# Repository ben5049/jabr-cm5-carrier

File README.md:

# Compute Module 5 Carrier Board (WIP)

Compact CM5 carrier board with an M.2 E-key connector and a 1000BASE-T1 ethernet PHY, as well as other optional IO.

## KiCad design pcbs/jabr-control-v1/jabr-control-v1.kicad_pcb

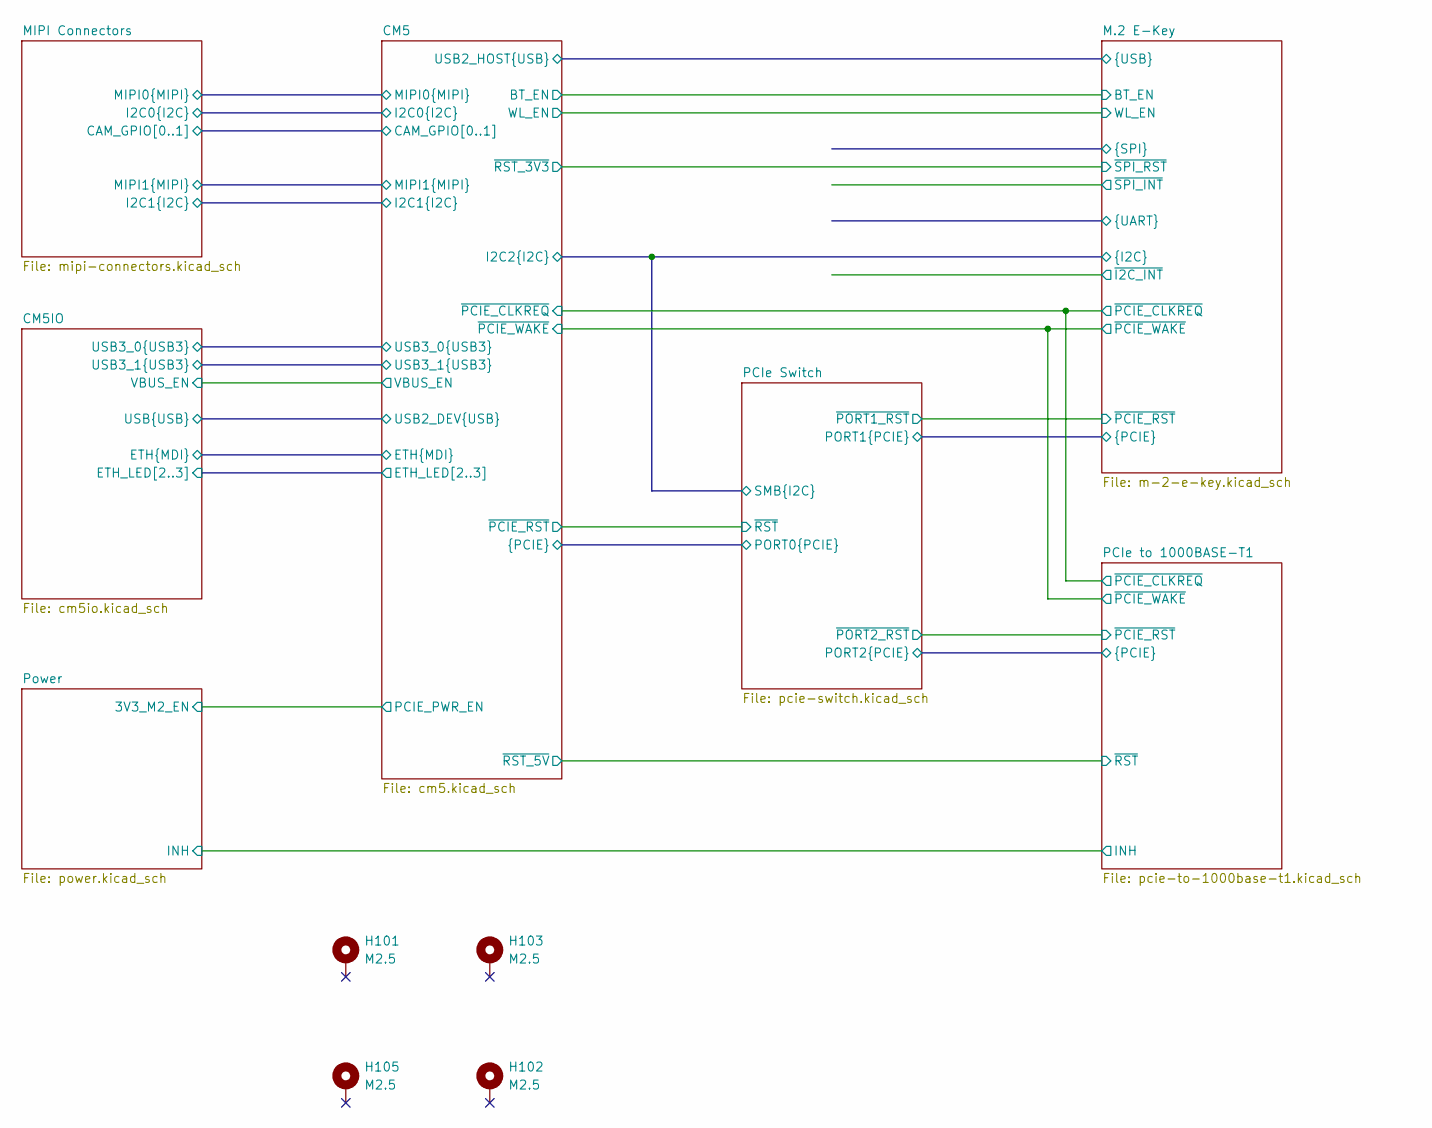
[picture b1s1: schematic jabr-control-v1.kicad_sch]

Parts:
H101, H102, H103, H105: M2.5; MountingHole_2.7mm_M2.5_Pad

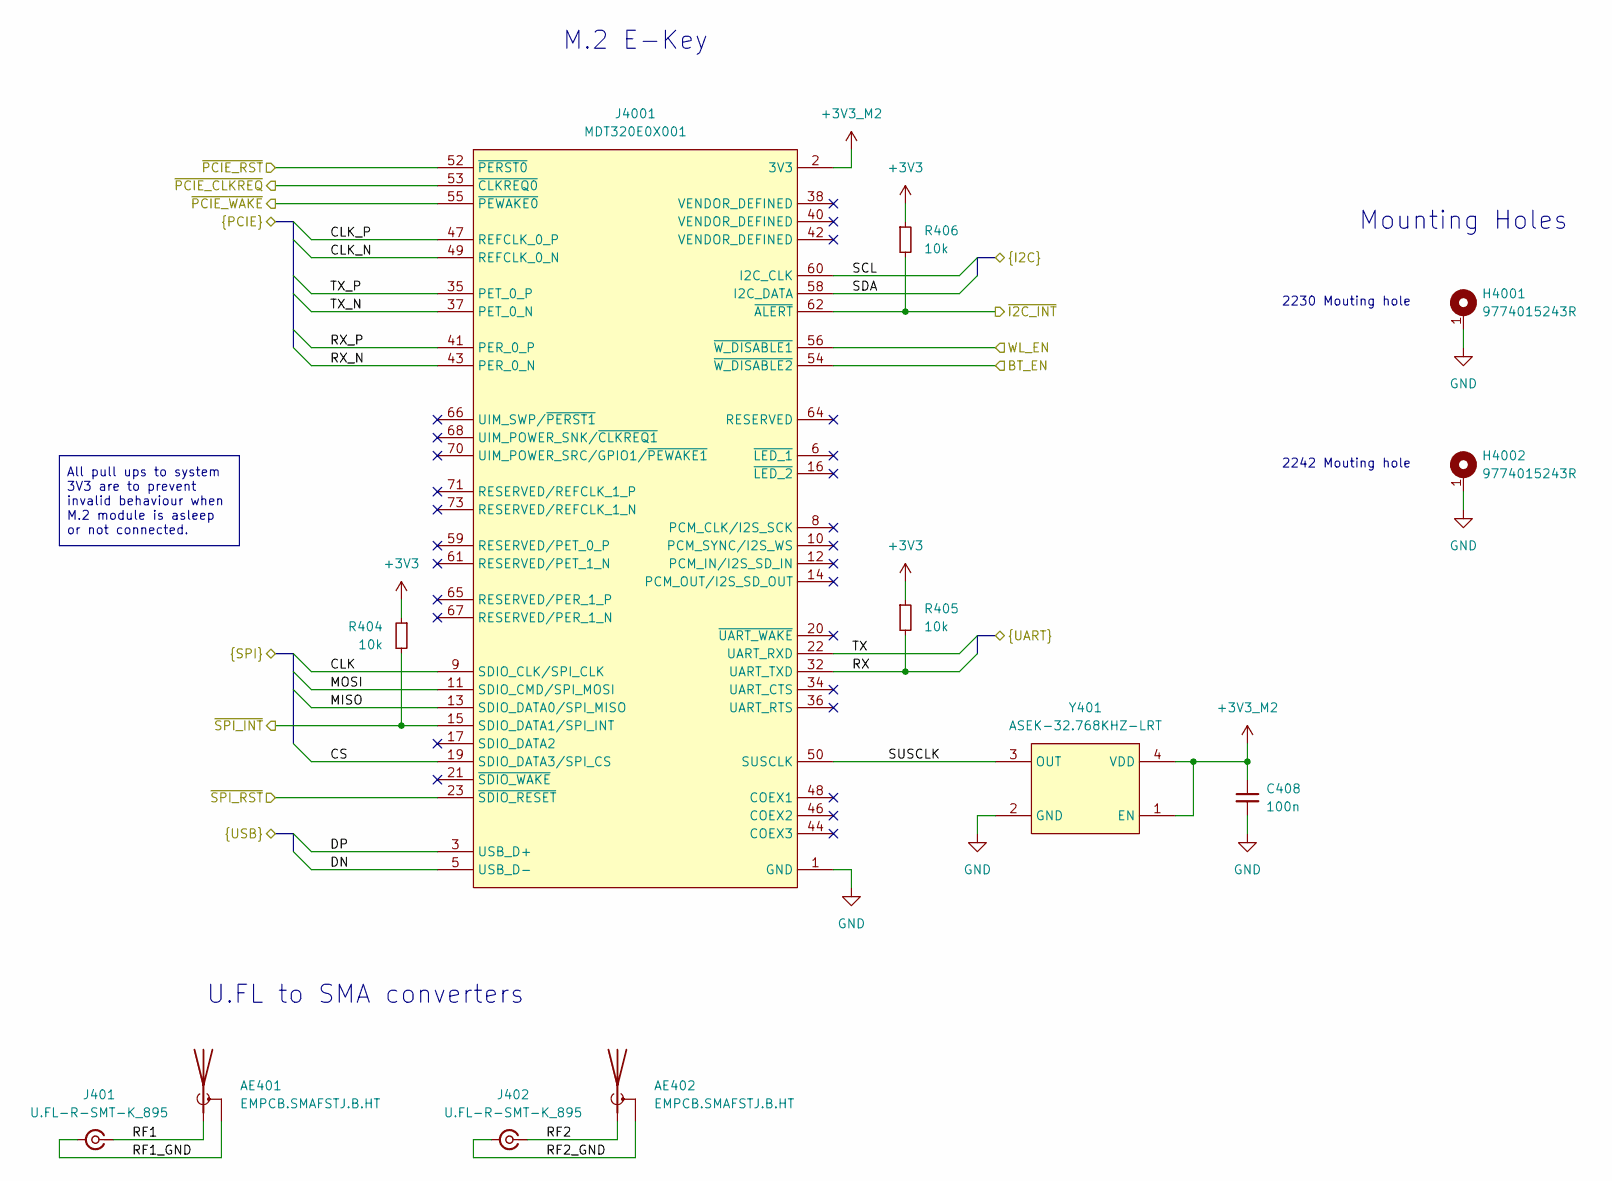
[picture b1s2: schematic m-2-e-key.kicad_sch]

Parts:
AE401, AE402: EMPCB.SMAFSTJ.B.HT; sma_edge_mount
C408: 100n
H4001, H4002: 9774015243R; 9774025243R
J401, J402: U.FL-R-SMT-K_895; UFLRSMTK895
J4001: MDT320E0X001; MDT420E0X001
R404, R405, R406: 10k; R_0402
Y401: ASEK-32.768KHZ-LRT; Crystal_SMD_3225-4Pin_3.2x2.5mm

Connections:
+3V3: R404.1, R405.1, R406.1; also elsewhere on the board
+3V3_M2: C408.1, J4001.2 (3V3), J4001.4 (3V3), J4001.72 (3V3), J4001.74 (3V3), Y401.1 (EN), Y401.4 (VDD); also elsewhere on the board
/CM5/BT_EN: J4001.54 (~W_DISABLE2); also elsewhere on the board
/CM5/I2C2.SCL: J4001.60 (I2C_CLK); also elsewhere on the board
/CM5/I2C2.SDA: J4001.58 (I2C_DATA); also elsewhere on the board
/CM5/USB2_HOST.DN: J4001.5 (USB_D-); also elsewhere on the board
/CM5/USB2_HOST.DP: J4001.3 (USB_D+); also elsewhere on the board
/CM5/WL_EN: J4001.56 (~W_DISABLE1); also elsewhere on the board
/CM5/~PCIE_CLKREQ: J4001.53 (~CLKREQ0); also elsewhere on the board
/CM5/~PCIE_WAKE: J4001.55 (~PEWAKE0); also elsewhere on the board
/CM5/~RST_3V3: J4001.23 (~SDIO_RESET); also elsewhere on the board
/M.2 E-Key/CLK: J4001.9 (SDIO_CLK/SPI_CLK)
/M.2 E-Key/CLK_N: J4001.49 (REFCLK_0_N); also elsewhere on the board
/M.2 E-Key/CLK_P: J4001.47 (REFCLK_0_P); also elsewhere on the board
/M.2 E-Key/CS: J4001.19 (SDIO_DATA3/SPI_CS)
/M.2 E-Key/MISO: J4001.13 (SDIO_DATA0/SPI_MISO)
/M.2 E-Key/MOSI: J4001.11 (SDIO_CMD/SPI_MOSI)
/M.2 E-Key/RF1: AE401.1 (A), J401.1 (In)
/M.2 E-Key/RF1_GND: AE401.2 (Shield), J401.2 (Ext)
/M.2 E-Key/RF2: AE402.1 (A), J402.1 (In)
/M.2 E-Key/RF2_GND: AE402.2 (Shield), J402.2 (Ext)
/M.2 E-Key/RX: J4001.32 (UART_TXD), R405.2
/M.2 E-Key/RX_N: J4001.43 (PER_0_N); also elsewhere on the board
/M.2 E-Key/RX_P: J4001.41 (PER_0_P); also elsewhere on the board
/M.2 E-Key/SUSCLK: J4001.50 (SUSCLK), Y401.3 (OUT)
/M.2 E-Key/TX: J4001.22 (UART_RXD)
/M.2 E-Key/TX_N: J4001.37 (PET_0_N); also elsewhere on the board
/M.2 E-Key/TX_P: J4001.35 (PET_0_P); also elsewhere on the board
/M.2 E-Key/~I2C_INT: J4001.62 (~ALERT), R406.2
/M.2 E-Key/~PCIE_RST: J4001.52 (~PERST0); also elsewhere on the board
/M.2 E-Key/~SPI_INT: J4001.15 (SDIO_DATA1/SPI_INT), R404.2
GND: C408.2, H4001.1, H4002.1, J4001.1 (GND), J4001.7 (GND), J4001.18 (GND), J4001.33 (GND), J4001.39 (GND), J4001.45 (GND), J4001.51 (GND), J4001.57 (GND), J4001.63 (GND), J4001.69 (GND), J4001.75 (GND), Y401.2 (GND); also elsewhere on the board

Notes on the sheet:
M.2 E-Key
2242 Mouting hole
U.FL to SMA converters
Mounting Holes
2230 Mouting hole
All pull ups to system 3V3 are to prevent invalid behaviour when M.2 module is asleep or not connected.

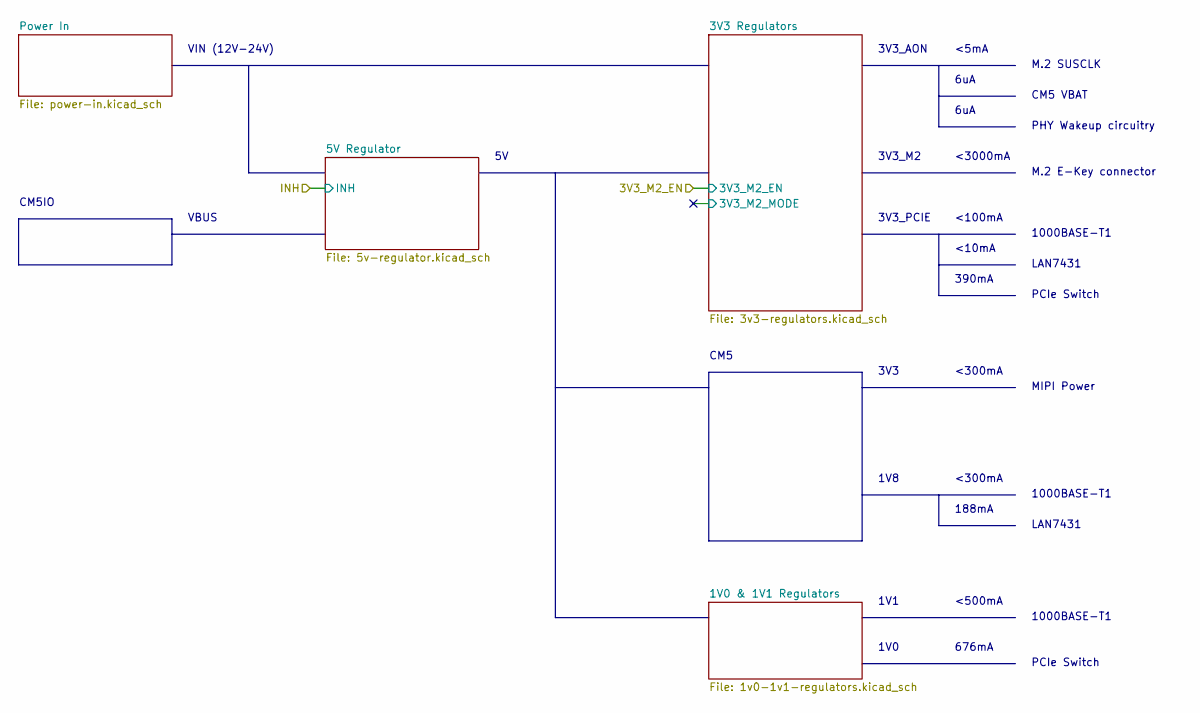
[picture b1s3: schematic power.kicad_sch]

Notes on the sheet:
PHY Wakeup circuitry
PCIe Switch
676mA
VBUS
<100mA
3V3
<300mA
6uA
3V3_M2
LAN7431
1V1
CM5IO
<5mA
1000BASE-T1
188mA
M.2 E-Key connector
3V3_PCIE
M.2 SUSCLK
<10mA
VIN (12V-24V)
<500mA
1V8
<3000mA
CM5 VBAT
3V3_AON
1V0
390mA
CM5
MIPI Power

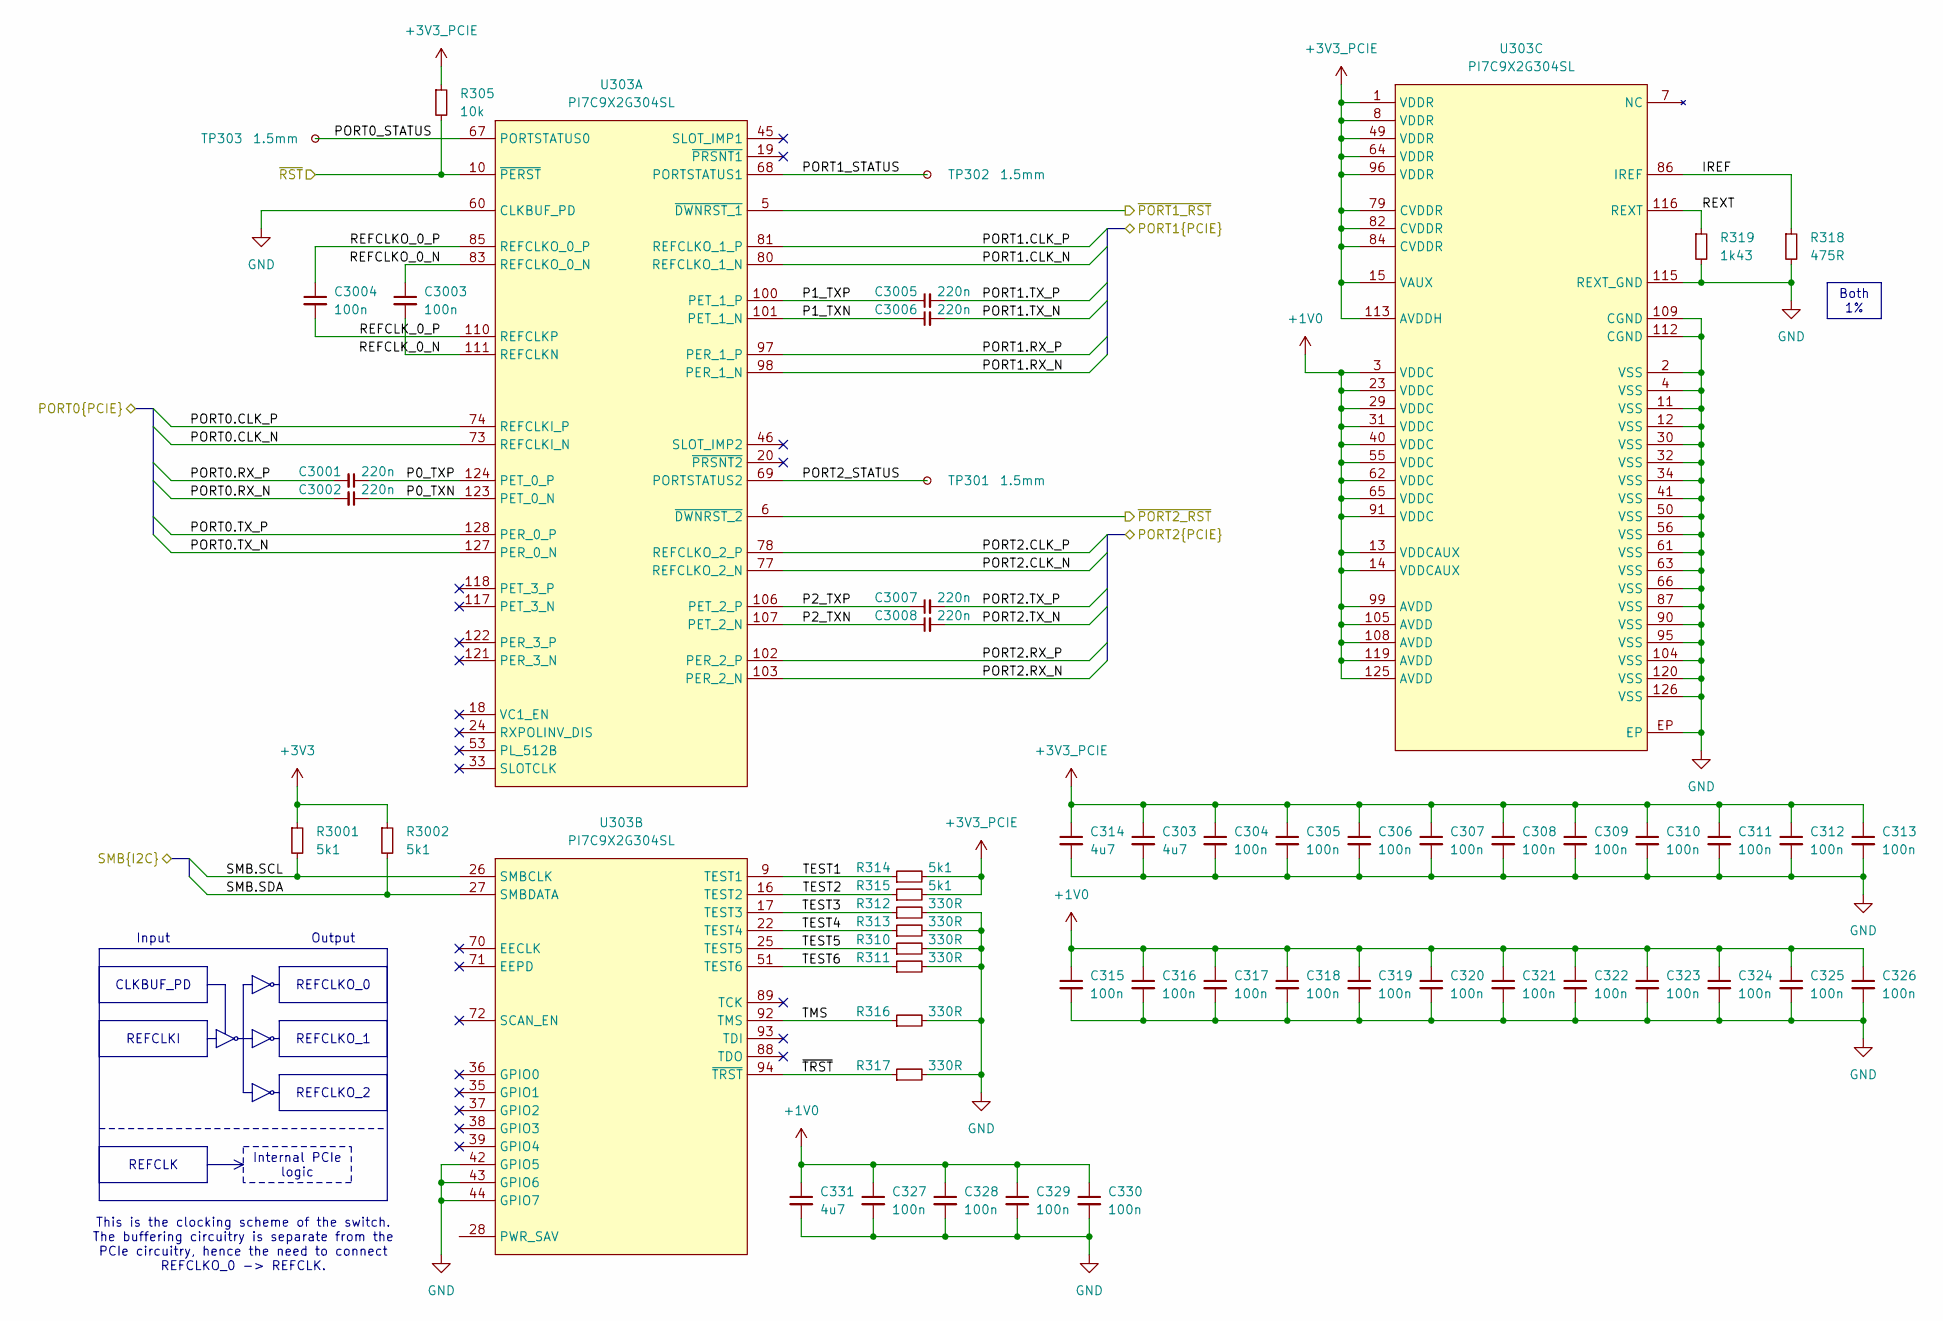
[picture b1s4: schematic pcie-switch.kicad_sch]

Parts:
C303, C314, C331: 4u7; C_0402
C304, C305, C306, C307, C308, C309, C310, C311, C312, C313, C315, C316, C317, C318, C319, C320, C321, C322, C323, C324, C325, C326, C327, C328, C329, C330, C3003, C3004: 100n; C_0402
C3001, C3002, C3005, C3006, C3007, C3008: 220n; C_0402
R305: 10k; R_0402
R310, R311, R312, R313, R316, R317: 330R
R314, R315: 5k1
R318: 475R; R_0402
R319: 1k43; R_0402
R3001, R3002: 5k1; R_0402
TP301, TP302, TP303: 1.5mm; TestPoint_Pad_D1.5mm
U303: PI7C9X2G304SL; QFP40P1600X1600X160-129N

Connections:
+1V0: C315.1, C316.1, C317.1, C318.1, C319.1, C320.1, C321.1, C322.1, C323.1, C324.1, C325.1, C326.1, C327.1, C328.1, C329.1, C330.1, C331.1, U303.3 (VDDC), U303.13 (VDDCAUX), U303.14 (VDDCAUX), U303.23 (VDDC), U303.29 (VDDC), U303.31 (VDDC), U303.40 (VDDC), U303.55 (VDDC), U303.62 (VDDC), U303.65 (VDDC), U303.91 (VDDC), U303.99 (AVDD), U303.105 (AVDD), U303.108 (AVDD), U303.119 (AVDD), U303.125 (AVDD); also elsewhere on the board
+3V3: R3001.1, R3002.1; also elsewhere on the board
+3V3_PCIE: C303.1, C304.1, C305.1, C306.1, C307.1, C308.1, C309.1, C310.1, C311.1, C312.1, C313.1, C314.1, R305.1, R314.2, R315.2, U303.1 (VDDR), U303.8 (VDDR), U303.15 (VAUX), U303.49 (VDDR), U303.64 (VDDR), U303.79 (CVDDR), U303.82 (CVDDR), U303.84 (CVDDR), U303.96 (VDDR), U303.113 (AVDDH); also elsewhere on the board
/CM5/CLK_N: U303.73 (REFCLKI_N); also elsewhere on the board
/CM5/CLK_P: U303.74 (REFCLKI_P); also elsewhere on the board
/CM5/I2C2.SCL: R3001.2, U303.26 (SMBCLK); also elsewhere on the board
/CM5/I2C2.SDA: R3002.2, U303.27 (SMBDATA); also elsewhere on the board
/CM5/RX_N: C3002.2; also elsewhere on the board
/CM5/RX_P: C3001.2; also elsewhere on the board
/CM5/TX_N: U303.127 (PER_0_N); also elsewhere on the board
/CM5/TX_P: U303.128 (PER_0_P); also elsewhere on the board
/CM5/~PCIE_RST: R305.2, U303.10 (~PERST); also elsewhere on the board
/M.2 E-Key/CLK_N: U303.80 (REFCLKO_1_N); also elsewhere on the board
/M.2 E-Key/CLK_P: U303.81 (REFCLKO_1_P); also elsewhere on the board
/M.2 E-Key/RX_N: U303.98 (PER_1_N); also elsewhere on the board
/M.2 E-Key/RX_P: U303.97 (PER_1_P); also elsewhere on the board
/M.2 E-Key/TX_N: C3006.2; also elsewhere on the board
/M.2 E-Key/TX_P: C3005.2; also elsewhere on the board
/M.2 E-Key/~PCIE_RST: U303.5 (~DWNRST_1); also elsewhere on the board
/PCIe Switch/IREF: R318.1, U303.86 (IREF)
/PCIe Switch/P0_TXN: C3002.1, U303.123 (PET_0_N)
/PCIe Switch/P0_TXP: C3001.1, U303.124 (PET_0_P)
/PCIe Switch/P1_TXN: C3006.1, U303.101 (PET_1_N)
/PCIe Switch/P1_TXP: C3005.1, U303.100 (PET_1_P)
/PCIe Switch/P2_TXN: C3008.1, U303.107 (PET_2_N)
/PCIe Switch/P2_TXP: C3007.1, U303.106 (PET_2_P)
/PCIe Switch/PORT0_STATUS: TP303.1, U303.67 (PORTSTATUS0)
/PCIe Switch/PORT1_STATUS: TP302.1, U303.68 (PORTSTATUS1)
/PCIe Switch/PORT2.CLK_N: U303.77 (REFCLKO_2_N); also elsewhere on the board
/PCIe Switch/PORT2.CLK_P: U303.78 (REFCLKO_2_P); also elsewhere on the board
/PCIe Switch/PORT2.RX_N: U303.103 (PER_2_N); also elsewhere on the board
/PCIe Switch/PORT2.RX_P: U303.102 (PER_2_P); also elsewhere on the board
/PCIe Switch/PORT2.TX_N: C3008.2; also elsewhere on the board
/PCIe Switch/PORT2.TX_P: C3007.2; also elsewhere on the board
/PCIe Switch/PORT2_STATUS: TP301.1, U303.69 (PORTSTATUS2)
/PCIe Switch/REFCLKO_0_N: C3003.1, U303.83 (REFCLKO_0_N)
/PCIe Switch/REFCLKO_0_P: C3004.1, U303.85 (REFCLKO_0_P)
/PCIe Switch/REFCLK_0_N: C3003.2, U303.111 (REFCLKN)
/PCIe Switch/REFCLK_0_P: C3004.2, U303.110 (REFCLKP)
/PCIe Switch/REXT: R319.1, U303.116 (REXT)
/PCIe Switch/TEST1: R314.1, U303.9 (TEST1)
/PCIe Switch/TEST2: R315.1, U303.16 (TEST2)
/PCIe Switch/TEST3: R312.1, U303.17 (TEST3)
/PCIe Switch/TEST4: R313.1, U303.22 (TEST4)
/PCIe Switch/TEST5: R310.1, U303.25 (TEST5)
/PCIe Switch/TEST6: R311.1, U303.51 (TEST6)
/PCIe Switch/TMS: R316.1, U303.92 (TMS)
/PCIe Switch/~PORT2_RST: U303.6 (~DWNRST_2); also elsewhere on the board
/PCIe Switch/~TRST: R317.1, U303.94 (~TRST)
GND: C303.2, C304.2, C305.2, C306.2, C307.2, C308.2, C309.2, C310.2, C311.2, C312.2, C313.2, C314.2, C315.2, C316.2, C317.2, C318.2, C319.2, C320.2, C321.2, C322.2, C323.2, C324.2, C325.2, C326.2, C327.2, C328.2, C329.2, C330.2, C331.2, R310.2, R311.2, R312.2, R313.2, R316.2, R317.2, R318.2, R319.2, U303.2 (VSS), U303.4 (VSS), U303.11 (VSS), U303.12 (VSS), U303.30 (VSS), U303.32 (VSS), U303.34 (VSS), U303.41 (VSS), U303.42 (GPIO5), U303.43 (GPIO6), U303.44 (GPIO7), U303.50 (VSS), U303.56 (VSS), U303.60 (CLKBUF_PD), U303.61 (VSS), U303.63 (VSS), U303.66 (VSS), U303.87 (VSS), U303.90 (VSS), U303.95 (VSS), U303.104 (VSS), U303.109 (CGND), U303.112 (CGND), U303.115 (REXT_GND), U303.120 (VSS), U303.126 (VSS), U303.EP; also elsewhere on the board

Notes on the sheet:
Input
This is the clocking scheme of the switch. The buffering circuitry is separate from the PCIe circuitry, hence the need to connect REFCLKO_0 -> REFCLK.
Output
Both 1%
REFCLK
REFCLKO_0
REFCLKO_2
REFCLKO_1
Internal PCIe logic
REFCLKI
CLKBUF_PD

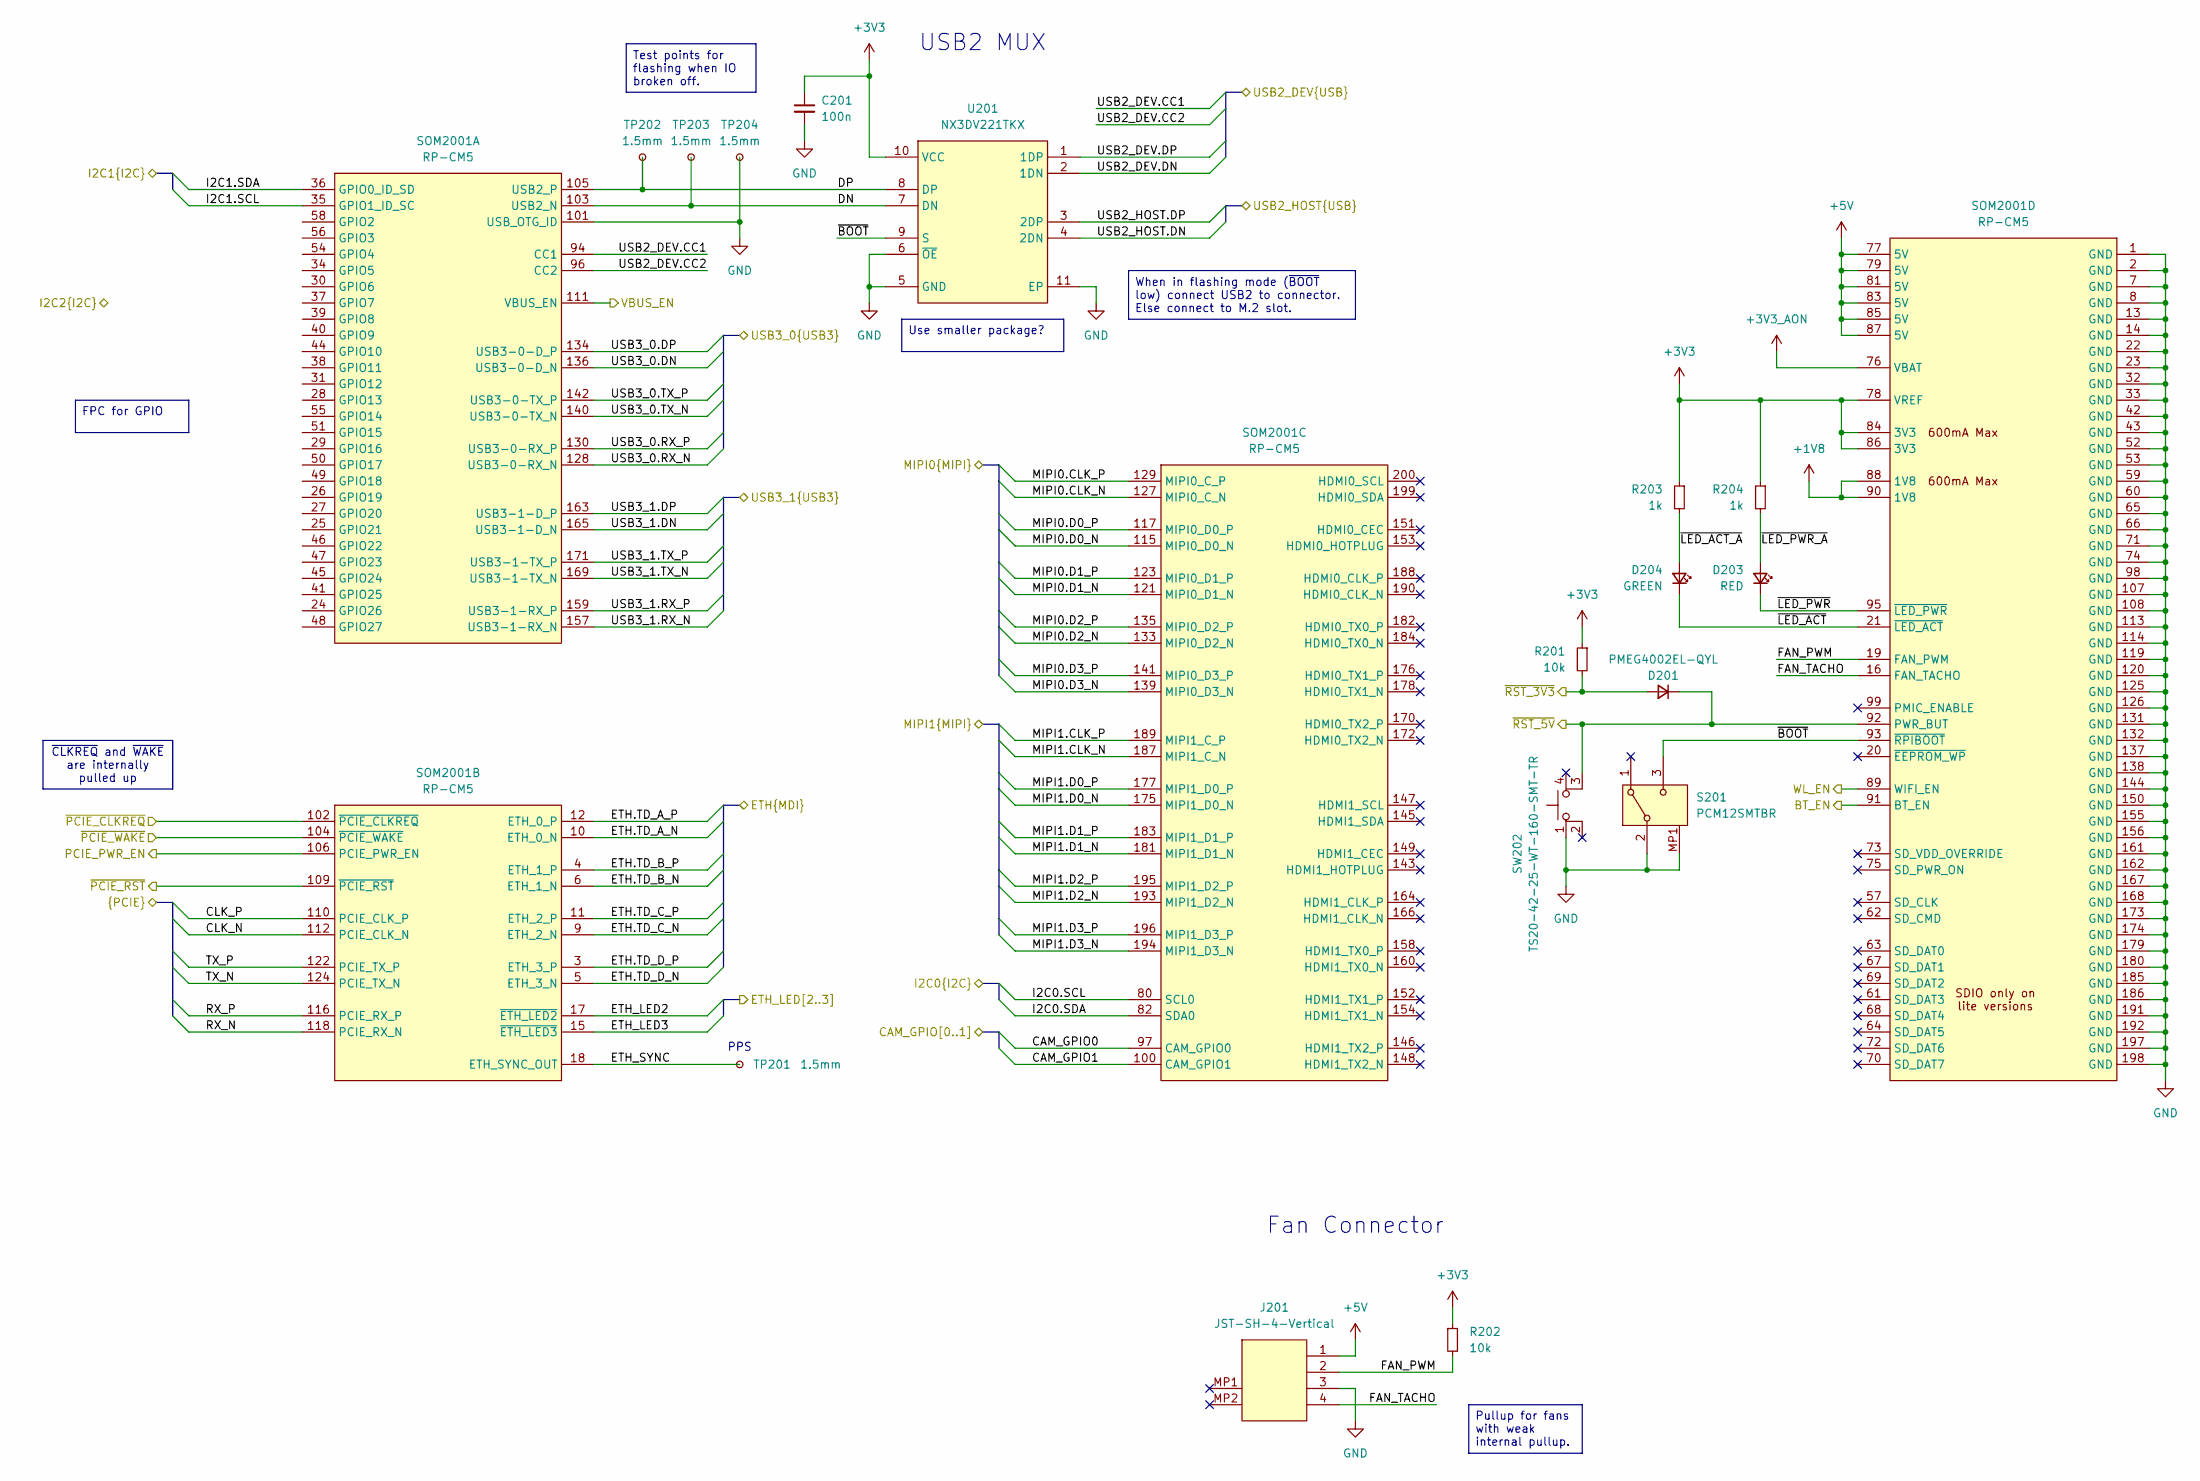
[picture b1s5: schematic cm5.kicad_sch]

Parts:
C201: 100n
D201: PMEG4002EL-QYL
D203: RED
D204: GREEN
J201: JST-SH-4-Vertical; JST_SH_BM04B-SRSS-TB_1x04-1MP_P1.00mm_Vertical
R201, R202: 10k; R_0402
R203, R204: 1k; R_0402
S201: PCM12SMTBR
SOM2001: RP-CM5; Raspberry-Pi-5-Compute-Module
SW202: TS20-42-25-WT-160-SMT-TR; TS204225WT160SMTTR; Mouser Part Number 179-TS204225WT160SMT
TP201, TP202, TP203, TP204: 1.5mm; TestPoint_Pad_D1.5mm
U201: NX3DV221TKX; SON50P300X300X100-11N

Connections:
+1V8: SOM2001.88 (1V8), SOM2001.90 (1V8); also elsewhere on the board
+3V3: C201.1, R201.1, R202.1, R203.1, R204.1, SOM2001.78 (VREF), SOM2001.84 (3V3), SOM2001.86 (3V3), U201.10 (VCC); also elsewhere on the board
+3V3_AON: SOM2001.76 (VBAT); also elsewhere on the board
+5V: J201.1, SOM2001.77 (5V), SOM2001.79 (5V), SOM2001.81 (5V), SOM2001.83 (5V), SOM2001.85 (5V), SOM2001.87 (5V); also elsewhere on the board
/CM5/BT_EN: SOM2001.91 (BT_EN); also elsewhere on the board
/CM5/CAM_GPIO0: SOM2001.97 (CAM_GPIO0)
/CM5/CAM_GPIO1: SOM2001.100 (CAM_GPIO1)
/CM5/CLK_N: SOM2001.112 (PCIE_CLK_N); also elsewhere on the board
/CM5/CLK_P: SOM2001.110 (PCIE_CLK_P); also elsewhere on the board
/CM5/DN: SOM2001.103 (USB2_N), TP203.1, U201.7 (DN)
/CM5/DP: SOM2001.105 (USB2_P), TP202.1, U201.8 (DP)
/CM5/ETH.TD_A_N: SOM2001.10 (ETH_0_N); also elsewhere on the board
/CM5/ETH.TD_A_P: SOM2001.12 (ETH_0_P); also elsewhere on the board
/CM5/ETH.TD_B_N: SOM2001.6 (ETH_1_N); also elsewhere on the board
/CM5/ETH.TD_B_P: SOM2001.4 (ETH_1_P); also elsewhere on the board
/CM5/ETH.TD_C_N: SOM2001.9 (ETH_2_N); also elsewhere on the board
/CM5/ETH.TD_C_P: SOM2001.11 (ETH_2_P); also elsewhere on the board
/CM5/ETH.TD_D_N: SOM2001.5 (ETH_3_N); also elsewhere on the board
/CM5/ETH.TD_D_P: SOM2001.3 (ETH_3_P); also elsewhere on the board
/CM5/ETH_LED2: SOM2001.17 (~ETH_LED2)
/CM5/ETH_LED3: SOM2001.15 (~ETH_LED3)
/CM5/ETH_SYNC: SOM2001.18 (ETH_SYNC_OUT), TP201.1
/CM5/FAN_PWM: J201.2, R202.2, SOM2001.19 (FAN_PWM)
/CM5/FAN_TACHO: J201.4, SOM2001.16 (FAN_TACHO)
/CM5/I2C0.SCL: SOM2001.80 (SCL0)
/CM5/I2C0.SDA: SOM2001.82 (SDA0)
/CM5/I2C1.SCL: SOM2001.35 (GPIO1_ID_SC)
/CM5/I2C1.SDA: SOM2001.36 (GPIO0_ID_SD)
/CM5/MIPI0.CLK_N: SOM2001.127 (MIPI0_C_N)
/CM5/MIPI0.CLK_P: SOM2001.129 (MIPI0_C_P)
/CM5/MIPI0.D0_N: SOM2001.115 (MIPI0_D0_N)
/CM5/MIPI0.D0_P: SOM2001.117 (MIPI0_D0_P)
/CM5/MIPI0.D1_N: SOM2001.121 (MIPI0_D1_N)
/CM5/MIPI0.D1_P: SOM2001.123 (MIPI0_D1_P)
/CM5/MIPI0.D2_N: SOM2001.133 (MIPI0_D2_N)
/CM5/MIPI0.D2_P: SOM2001.135 (MIPI0_D2_P)
/CM5/MIPI0.D3_N: SOM2001.139 (MIPI0_D3_N)
/CM5/MIPI0.D3_P: SOM2001.141 (MIPI0_D3_P)
/CM5/MIPI1.CLK_N: SOM2001.187 (MIPI1_C_N)
/CM5/MIPI1.CLK_P: SOM2001.189 (MIPI1_C_P)
/CM5/MIPI1.D0_N: SOM2001.175 (MIPI1_D0_N)
/CM5/MIPI1.D0_P: SOM2001.177 (MIPI1_D0_P)
/CM5/MIPI1.D1_N: SOM2001.181 (MIPI1_D1_N)
/CM5/MIPI1.D1_P: SOM2001.183 (MIPI1_D1_P)
/CM5/MIPI1.D2_N: SOM2001.193 (MIPI1_D2_N)
/CM5/MIPI1.D2_P: SOM2001.195 (MIPI1_D2_P)
/CM5/MIPI1.D3_N: SOM2001.194 (MIPI1_D3_N)
/CM5/MIPI1.D3_P: SOM2001.196 (MIPI1_D3_P)
/CM5/PCIE_PWR_EN: SOM2001.106 (PCIE_PWR_EN); also elsewhere on the board
/CM5/RX_N: SOM2001.118 (PCIE_RX_N); also elsewhere on the board
/CM5/RX_P: SOM2001.116 (PCIE_RX_P); also elsewhere on the board
/CM5/TX_N: SOM2001.124 (PCIE_TX_N); also elsewhere on the board
/CM5/TX_P: SOM2001.122 (PCIE_TX_P); also elsewhere on the board
/CM5/USB2_DEV.CC1: SOM2001.94 (CC1); also elsewhere on the board
/CM5/USB2_DEV.CC2: SOM2001.96 (CC2); also elsewhere on the board
/CM5/USB2_DEV.DN: U201.2 (1DN); also elsewhere on the board
/CM5/USB2_DEV.DP: U201.1 (1DP); also elsewhere on the board
/CM5/USB2_HOST.DN: U201.4 (2DN); also elsewhere on the board
/CM5/USB2_HOST.DP: U201.3 (2DP); also elsewhere on the board
/CM5/USB3_0.DN: SOM2001.136 (USB3-0-D_N); also elsewhere on the board
/CM5/USB3_0.DP: SOM2001.134 (USB3-0-D_P); also elsewhere on the board
/CM5/USB3_0.RX_N: SOM2001.128 (USB3-0-RX_N); also elsewhere on the board
/CM5/USB3_0.RX_P: SOM2001.130 (USB3-0-RX_P); also elsewhere on the board
/CM5/USB3_0.TX_N: SOM2001.140 (USB3-0-TX_N); also elsewhere on the board
/CM5/USB3_0.TX_P: SOM2001.142 (USB3-0-TX_P); also elsewhere on the board
/CM5/USB3_1.DN: SOM2001.165 (USB3-1-D_N); also elsewhere on the board
/CM5/USB3_1.DP: SOM2001.163 (USB3-1-D_P); also elsewhere on the board
/CM5/USB3_1.RX_N: SOM2001.157 (USB3-1-RX_N); also elsewhere on the board
/CM5/USB3_1.RX_P: SOM2001.159 (USB3-1-RX_P); also elsewhere on the board
/CM5/USB3_1.TX_N: SOM2001.169 (USB3-1-TX_N); also elsewhere on the board
/CM5/USB3_1.TX_P: SOM2001.171 (USB3-1-TX_P); also elsewhere on the board
/CM5/VBUS_EN: SOM2001.111 (VBUS_EN); also elsewhere on the board
/CM5/WL_EN: SOM2001.89 (WIFI_EN); also elsewhere on the board
/CM5/~BOOT: S201.3 (NO), SOM2001.93 (~RPIBOOT), U201.9 (S)
/CM5/~LED_ACT_A: D204.2 (A), R203.2
/CM5/~LED_ACT: D204.1 (K), SOM2001.21 (~LED_ACT)
/CM5/~LED_PWR_A: D203.2 (A), R204.2
/CM5/~LED_PWR: D203.1 (K), SOM2001.95 (~LED_PWR)
/CM5/~PCIE_CLKREQ: SOM2001.102 (~PCIE_CLKREQ); also elsewhere on the board
/CM5/~PCIE_RST: SOM2001.109 (~PCIE_RST); also elsewhere on the board
/CM5/~PCIE_WAKE: SOM2001.104 (~PCIE_WAKE); also elsewhere on the board
/CM5/~RST_3V3: D201.2 (A), R201.2; also elsewhere on the board
/CM5/~RST_5V: D201.1 (K), SOM2001.92 (PWR_BUT), SW202.3; also elsewhere on the board
GND: C201.2, J201.3, S201.2 (COM), S201.MP1, S201.MP2, S201.MP3, S201.MP4, SOM2001.1 (GND), SOM2001.2 (GND), SOM2001.7 (GND), SOM2001.8 (GND), SOM2001.13 (GND), SOM2001.14 (GND), SOM2001.22 (GND), SOM2001.23 (GND), SOM2001.32 (GND), SOM2001.33 (GND), SOM2001.42 (GND), SOM2001.43 (GND), SOM2001.52 (GND), SOM2001.53 (GND), SOM2001.59 (GND), SOM2001.60 (GND), SOM2001.65 (GND), SOM2001.66 (GND), SOM2001.71 (GND), SOM2001.74 (GND), SOM2001.98 (GND), SOM2001.101 (USB_OTG_ID), SOM2001.107 (GND), SOM2001.108 (GND), SOM2001.113 (GND), SOM2001.114 (GND), SOM2001.119 (GND), SOM2001.120 (GND), SOM2001.125 (GND), SOM2001.126 (GND), SOM2001.131 (GND), SOM2001.132 (GND), SOM2001.137 (GND), SOM2001.138 (GND), SOM2001.144 (GND), SOM2001.150 (GND), SOM2001.155 (GND), SOM2001.156 (GND), SOM2001.161 (GND), SOM2001.162 (GND), SOM2001.167 (GND), SOM2001.168 (GND), SOM2001.173 (GND), SOM2001.174 (GND), SOM2001.179 (GND), SOM2001.180 (GND), SOM2001.185 (GND), SOM2001.186 (GND), SOM2001.191 (GND), SOM2001.192 (GND), SOM2001.197 (GND), SOM2001.198 (GND), SW202.1, TP204.1, U201.5 (GND), U201.6 (~OE), U201.11 (EP); also elsewhere on the board

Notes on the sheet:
PPS
Fan Connector
USB2 MUX
When in flashing mode (~{BOOT} low) connect USB2 to connector. Else connect to M.2 slot.
Use smaller package?
FPC for GPIO
~{CLKREQ} and ~{WAKE} are internally pulled up
Pullup for fans with weak internal pullup.
Test points for flashing when IO broken off.

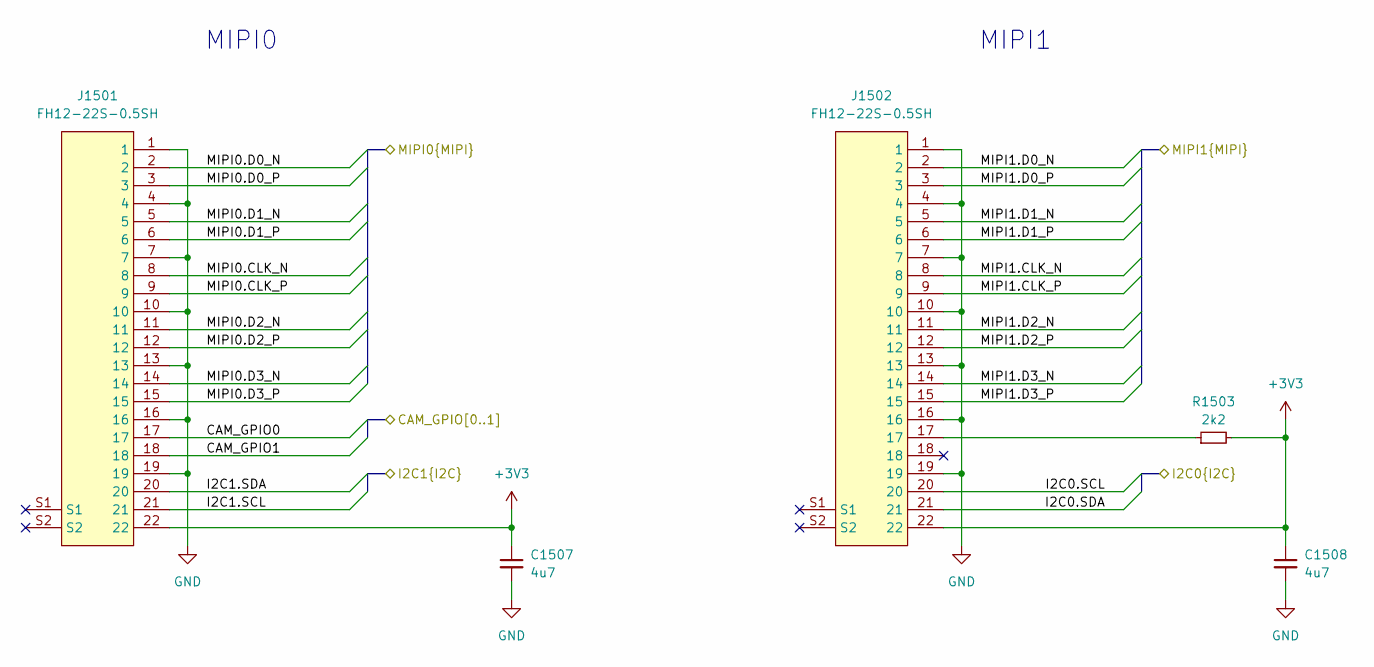
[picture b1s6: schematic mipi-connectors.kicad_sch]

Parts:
C1507, C1508: 4u7; C_0402
J1501, J1502: FH12-22S-0.5SH
R1503: 2k2

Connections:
+3V3: C1507.1, C1508.1, J1501.22, J1502.22, R1503.2; also elsewhere on the board
GND: C1507.2, C1508.2, J1501.1, J1501.4, J1501.7, J1501.10, J1501.13, J1501.16, J1501.19, J1502.1, J1502.4, J1502.7, J1502.10, J1502.13, J1502.16, J1502.19; also elsewhere on the board
unnamed: J1502.17, R1503.1

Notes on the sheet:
MIPI1
MIPI0
